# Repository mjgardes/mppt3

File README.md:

mppt3
=====
Software and hardware designs for DC-DC power conversion with max power point tracking and lots of other cool features for PV applications.

Software runs on a Beaglebone Black.  The goal is to have up to three analog boards stack on top of that.  Although the way I'm driving the boards now, I could go up to eight. Maybe eleven if I figure out how to build kernel modules.  Each analog module would be optimizing one panel to eke out every last possible mW.

My goal was to have this somewhat working by July '14.

See the wiki for current progress

If you have suggestions or feature requests or whatever, I'm all ears.  Or even if you find a product out there that does this better.

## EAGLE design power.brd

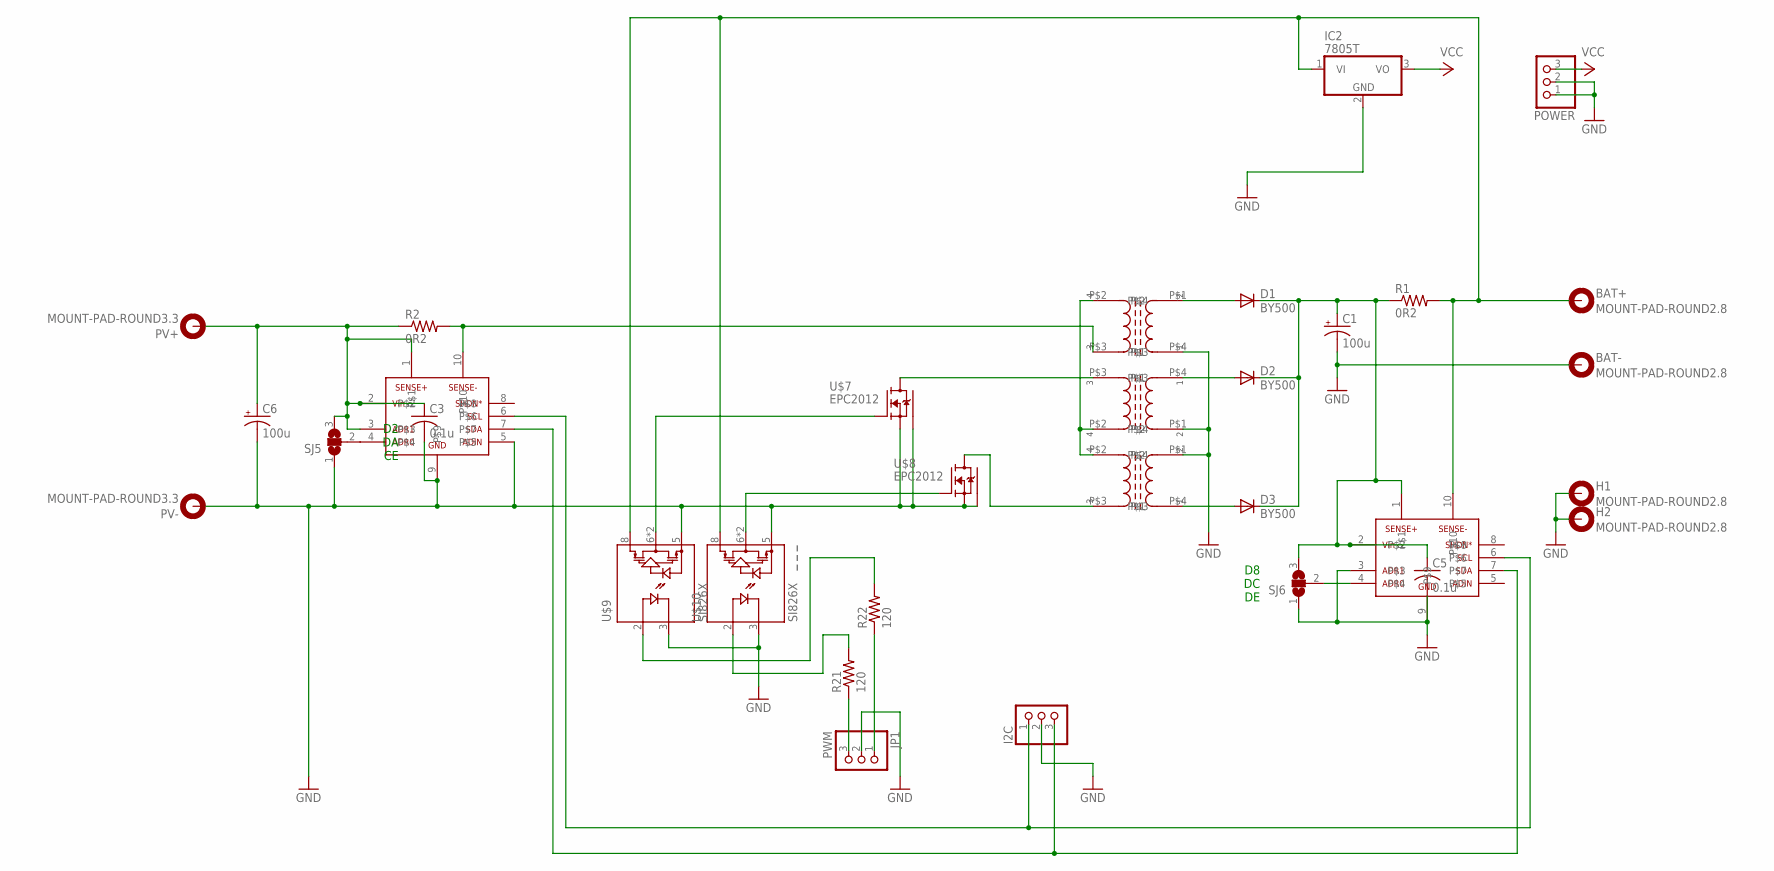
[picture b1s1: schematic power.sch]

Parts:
BAT+: MOUNT-PAD-ROUND2.8; 2,8-PAD
BAT-: MOUNT-PAD-ROUND2.8; 2,8-PAD
C1, C6: 100u; E5-10,5
C3, C5: 0.1u; C0603K
D1, D2, D3: BY500; DO201-15
H1, H2: MOUNT-PAD-ROUND2.8; 2,8-PAD
I2C: PINHD-1X3; 1X03
IC2: 7805T; TO220H
JP1: PWM; 1X03
POWER: PINHD-1X3; 1X03
PV+: MOUNT-PAD-ROUND3.3; 3,3-PAD
PV-: MOUNT-PAD-ROUND3.3; 3,3-PAD
R1, R2: 0R2; R1206
R21, R22: 120; R0603
SJ5, SJ6: SJ2W; SJ_2
U$1, U$2: LTC4151; MSOP10
U$3: PLH10AN2211R5P2B; L10-13
U$4, U$5: TLF14CBH3321R0K1; L13-17
U$7, U$8: EPC2012; EGAN-DIE-7
U$9, U$10: SI826X; SO08

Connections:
GND: BAT-.B2,8, C1.-, C3.2, C5.2, C6.-, H1.B2,8, H2.B2,8, I2C.2, IC2.2 (GND), JP1.2, POWER.1, POWER.2, PV-.B3,3, SJ5.1, SJ6.1, U$1.5, U$1.9, U$2.3, U$2.9, U$3.P$4, U$4.P$1, U$5.P$1, U$7.SOURCE (S), U$7.SUBSTRATE, U$8.SOURCE (S), U$8.SUBSTRATE, U$9.3 (GND1), U$9.5 (GND2), U$10.3 (GND1), U$10.5 (GND2)
unnamed: U$3.P$2, U$4.P$2, U$5.P$2
unnamed: U$5.P$3, U$7.DRAIN (D)
unnamed: U$4.P$3, U$8.DRAIN (D)
unnamed: BAT+.B2,8, IC2.1 (VI), R1.2, U$2.10, U$9.8 (VDD2), U$10.8 (VDD2)
unnamed: D3.A, U$4.P$4
unnamed: R21.2, U$10.2 (VI)
unnamed: D2.A, U$5.P$4
unnamed: SJ5.2, U$1.4
unnamed: C1.+, C5.1, D1.C, D2.C, D3.C, R1.1, SJ6.3, U$2.1, U$2.2
unnamed: U$8.GATE (G), U$10.6 (VO), U$10.7 (VO)
unnamed: D1.A, U$3.P$1
unnamed: U$7.GATE (G), U$9.6 (VO), U$9.7 (VO)
unnamed: SJ6.2, U$2.4
unnamed: JP1.3, R21.1
unnamed: JP1.1, R22.1
unnamed: R22.2, U$9.2 (VI)
PV: C3.1, C6.+, PV+.B3,3, R2.1, SJ5.3, U$1.1, U$1.2, U$1.3
PVIN: R2.2, U$1.10, U$3.P$3
SCL: I2C.1, U$1.6, U$2.6
SDA: I2C.3, U$1.7, U$2.7
VCC: IC2.3 (VO), POWER.3

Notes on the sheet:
D2 DA CE
D8 DC DE

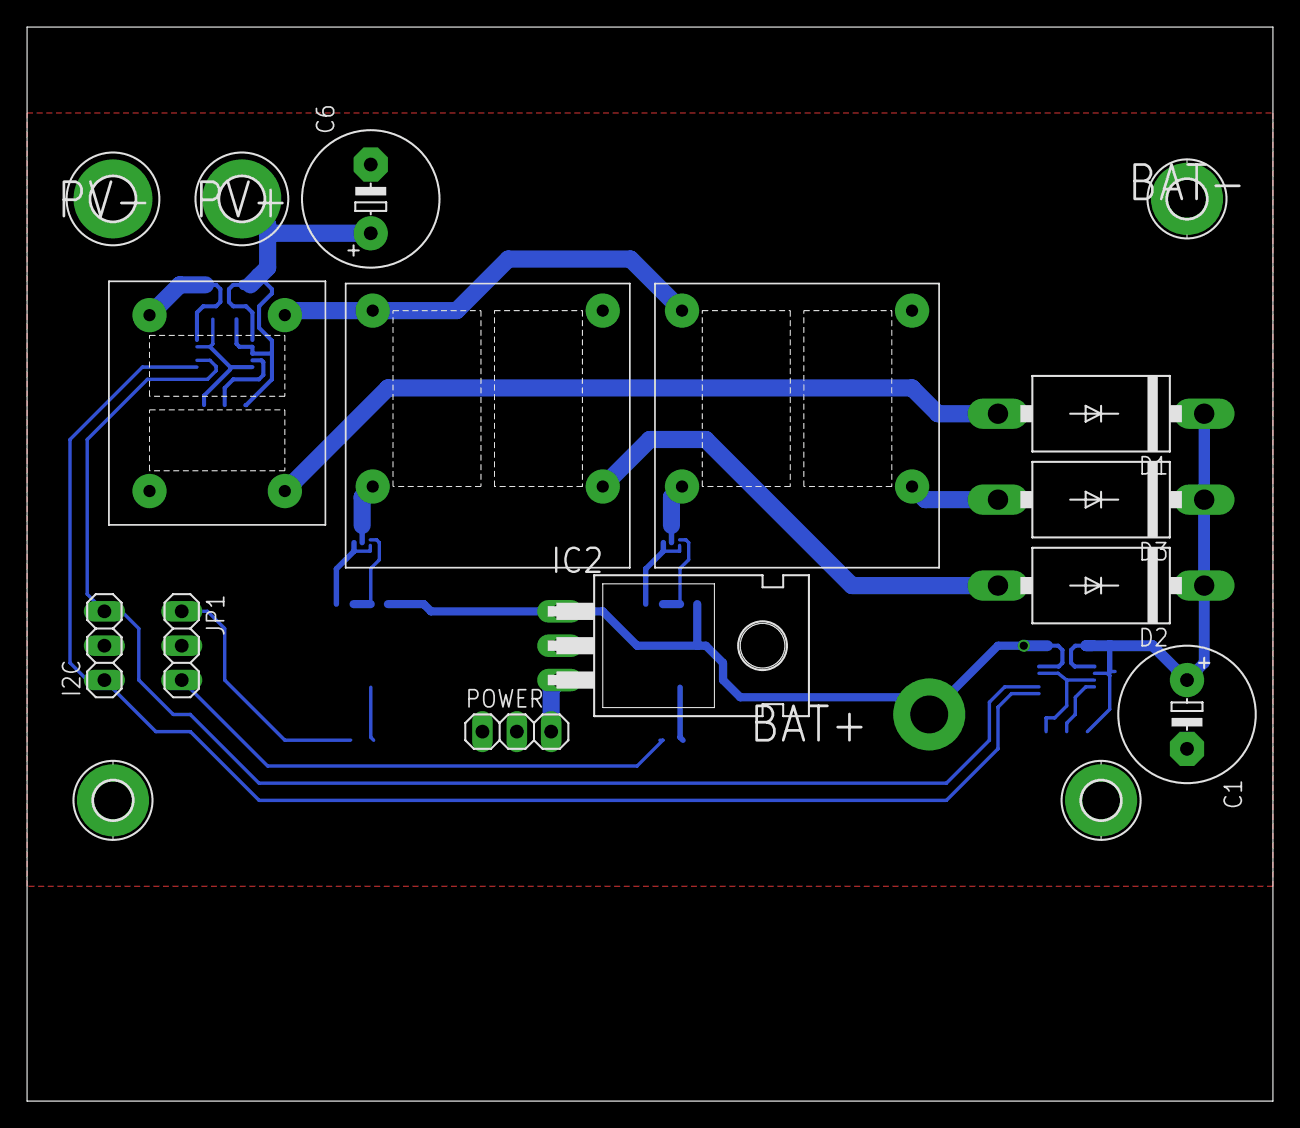
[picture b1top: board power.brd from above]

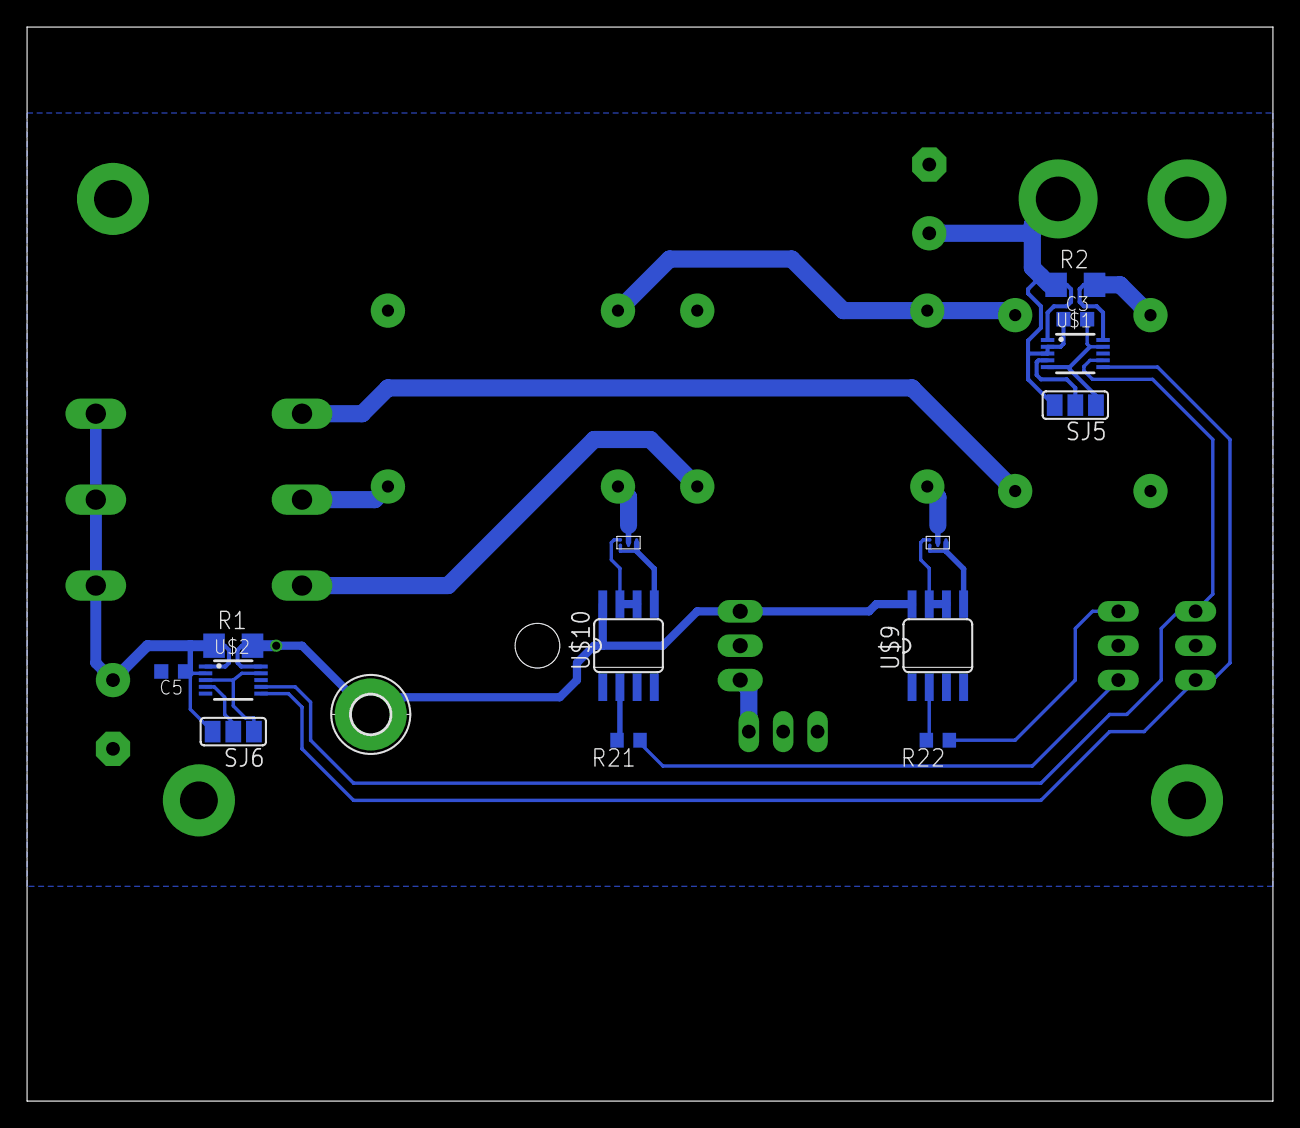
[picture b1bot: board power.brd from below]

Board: 2 copper layers, 92.1 x 79.4 mm, 32 parts (15 on the bottom side), 22 nets.

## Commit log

2014-03-04 hacking things together
2014-03-04 Transformer footprints and really awful looking board routing
    Pretty sure at least one of the transformers is wired in the wrong way
    too
2014-03-05 little tweaks
2014-03-06 fiddling with the layout
2014-03-06 proposed beaglebone connections and resistor dividers
2014-03-06 change all the things
2014-03-06 schematic might be correct. board is routed. no idea if it's routed well.
2014-03-06 better ground paths
2014-03-07 fixed a lot of things. confidence that this could work is up to 1%.
2014-03-07 I'm starting to like this layout. Not sure why.
2014-03-09 built a prototype, characterized it, and realized that i have the transformers swapped around. :(
2014-03-10 Corrected choke packages in library
    Rerouted board to reflect library changes
2014-03-17 Tried to make a device tree overlay
2014-03-17 Analog GND
    This might be important.
2014-03-17 broken device tree. just making a backup. move along, nothing to see here.
2014-03-18 some board fixes
2014-03-18 device tree overlay seems to work for the PWM part. use the analog helper for now until i feel like pasting it in.
2014-03-18 more board and schematic fixes. added slightly negative voltage reference hack.
2014-03-18 going to start a python script that does the dirty work
2014-03-18 backup
2014-03-20 back to the drawing board, i guess
2014-03-25 made things more complicated, fixed a schematic mistake, added gate drivers
2014-03-25 fixed more things, probably broke more things in the process
2014-03-25 fixed more things that had been bothering me.
2014-03-26 Schematic cleanup
    Thanks, Roger!
2014-03-26 Fixed the schematic, rerouted the board
2014-04-01 Nothing important, I hope
2014-04-02 stuff
2014-04-06 did you try reversing the polarity?
2014-04-16 wait for the next one...
2014-04-22 Removing all the failed ideas
    Everything may be broken
2014-04-29 added LTC4151 I2C IV monotors to the schematic and some other fixes. The prototype doesn't work yet, so watch out.
2014-04-30 whomp
2014-04-30 don't worry, it's not as bad as it looks
2014-04-30 still working on it
2014-04-30 almost there
2014-04-30 need a snapshot here
2014-04-30 LETS HOOK UP THE MOSFETS THE RIGHT WAY, OKAY?
2014-04-30 i'm pretty sure i had the FETs in the right way in the first place, actually...
2014-05-04 circuit rework in progress
2014-05-05 more optoisolation
2014-05-05 still more things to fix
2014-05-05 board
2014-05-05 board should be okay
2014-05-05 sending out for another prototype
2014-05-05 eps files just because
2014-05-05 just to make sure i got everything
2014-05-05 PDF of schematic
2014-05-05 fixed labels
2014-05-05 input capacitor? might help.
2014-05-05 sent out to board fab
2014-05-24 stencil
2014-05-24 hpgl... because why not
2014-05-29 important fixes... and that 7812 that isn't actually a 7812 is still a problem
2014-05-30 ****ing pinouts
2014-05-30 found more mistakes in the isolated i2c bus
2014-06-06 clean up after what should be a trivial merge
2014-06-06 7-bit i2c addresses to reduce confusion
2014-06-06 Cluttering up the schematic some more
2014-07-24 Pulled the hard stuff out of the schematic Still needs some work and a board redo
2014-07-25 Snapshotting here before changing things a lot
2014-10-30 Redid the board. Simplified everything and switched to GaN FETs.
2015-01-13 board revamp and LTspice schematic
2015-01-14 working simulation
2015-01-14 sim stuff
